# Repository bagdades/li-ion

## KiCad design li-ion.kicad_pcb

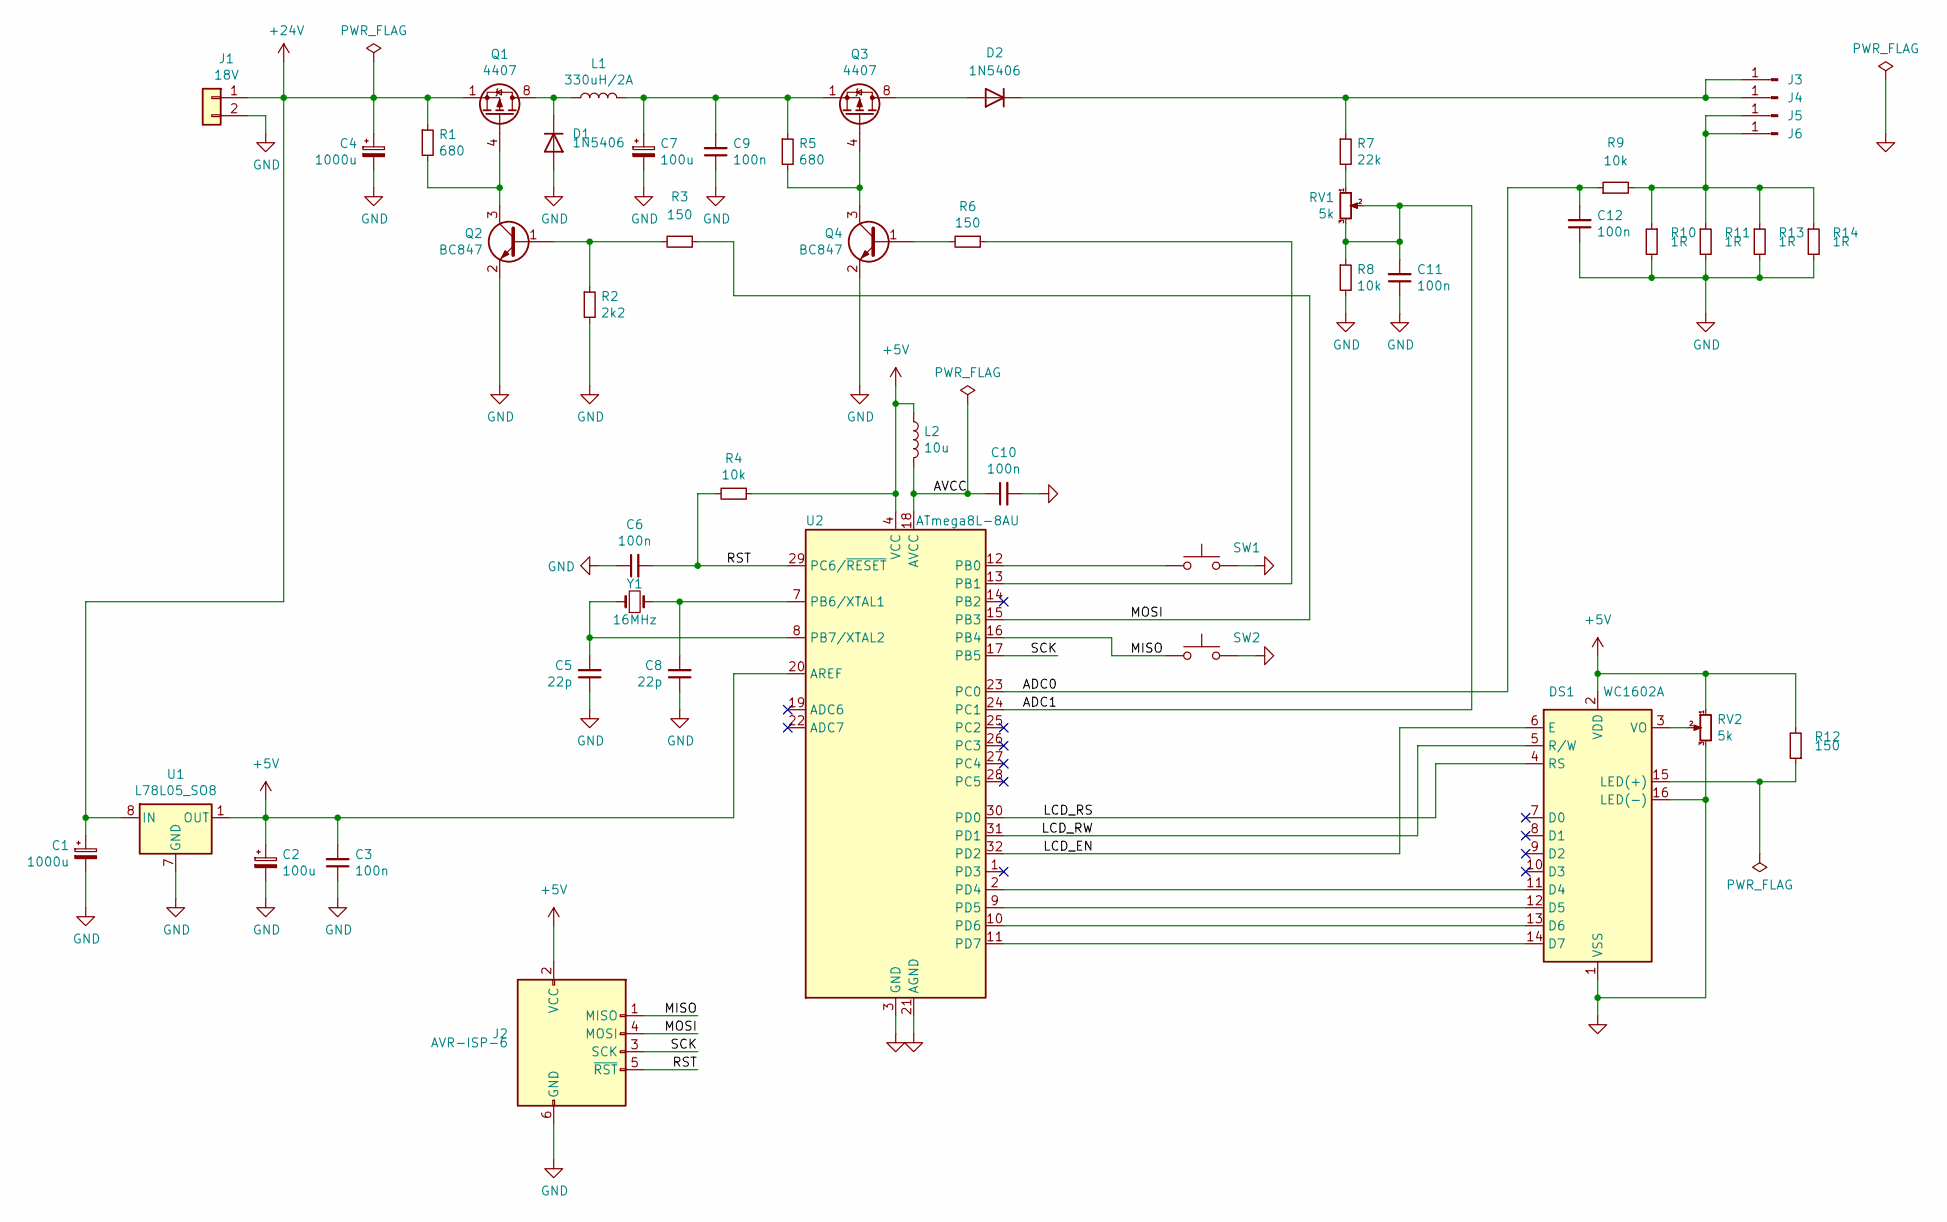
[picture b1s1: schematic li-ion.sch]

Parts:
C1, C4: 1000u; C_Radial_D10.0mm_H16.0mm_P5.00mm
C2: 100u; C_Radial_D8.0mm_H7.0mm_P3.50mm
C3, C6, C9, C10, C11, C12: 100n; C_0805_2012Metric
C5, C8: 22p; C_0603_1608Metric
C7: 100u; C_Radial_D10.0mm_H16.0mm_P5.00mm
D1, D2: 1N5406; D_DO-201AD_P15.24mm_Horizontal
DS1: WC1602A; PinHeader_1x16_P2.54mm_Vertical
J1: 18V; TerminalBlock_Phoenix_MKDS-1,5-2-5.08_1x02_P5.08mm_Horizont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
J2: AVR-ISP-6; PinHeader_2x03_P2.54mm_Vertical
J3, J4, J5, J6: Conn_01x01_Male; PinHeader_1x01_P2.54mm_Vertical
L1: 330uH/2A; L_Radial_D12.0mm_P5.00mm_Fastron_11P
L2: 10u; L_6.3x6.3_H3
Q1, Q3: 4407; SOIC-8_3.9x4.9mm_P1.27mm
Q2, Q4: BC847; SOT-23
R1, R5: 680; R_0805_2012Metric
R2: 2k2; R_0805_2012Metric
R3, R6, R12: 150; R_0805_2012Metric
R4, R8, R9: 10k; R_0805_2012Metric
R7: 22k; R_0805_2012Metric
R10, R11: 1R; R_1206_3216Metric
R13, R14: 1R; R_Axial_DIN0516_L15.5mm_D5.0mm_P20.32mm_Horizontal
RV1, RV2: 5k; Potentiometer_Piher_PT-6-V_Vertical
SW1, SW2: SW_Push; SW_Tactile_SPST_Angled_PTS645Vx58-2LFS
U1: L78L05_SO8; SOIC-8_3.9x4.9mm_P1.27mm
U2: ATmega8L-8AU; TQFP-32_7x7mm_P0.8mm
Y1: 16MHz; Crystal_HC18-U_Vertical

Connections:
+5V: C2.1, C3.2, DS1.2 (VDD), J2.2 (VCC), L2.1, R4.1, R12.2, RV2.1, U1.1 (OUT), U2.4 (VCC), U2.6 (VCC), U2.20 (AREF)
+24V: C1.1, C4.1, J1.1, Q1.1 (S), Q1.2 (S), Q1.3 (S), R1.1, U1.8 (IN)
/ADC0: C12.2, R9.1, U2.23 (PC0)
/ADC1: C11.2, R8.1, RV1.2, RV1.3, U2.24 (PC1)
/AVCC: C10.1, L2.2, U2.18 (AVCC)
/LCD_EN: DS1.6 (E), U2.32 (PD2)
/LCD_RS: DS1.4 (RS), U2.30 (PD0)
/LCD_RW: DS1.5 (R/W), U2.31 (PD1)
/MISO: J2.1 (MISO), SW2.1, U2.16 (PB4)
/MOSI: J2.4 (MOSI), R3.1, U2.15 (PB3)
/RST: C6.2, J2.5 (~RST), R4.2, U2.29 (PC6/~RESET)
/SCK: J2.3 (SCK), U2.17 (PB5)
GND: C1.2, C2.2, C3.1, C4.2, C5.1, C6.1, C7.2, C8.1, C9.1, C10.2, C11.1, C12.1, D1.2 (A), DS1.1 (VSS), DS1.16 (LED(-)), J1.2, J2.6 (GND), Q2.2 (E), Q4.2 (E), R2.2, R8.2, R10.2, R11.2, R13.2, R14.2, RV2.3, SW1.2, SW2.2, U1.2 (GND), U1.3 (GND), U1.6 (GND), U1.7 (GND), U2.3 (GND), U2.5 (GND), U2.21 (AGND)
unnamed: C5.2, U2.8 (PB7/XTAL2), Y1.1
unnamed: C7.1, C9.2, L1.2, Q3.1 (S), Q3.2 (S), Q3.3 (S), R5.1
unnamed: C8.2, U2.7 (PB6/XTAL1), Y1.2
unnamed: D1.1 (K), L1.1, Q1.5 (D), Q1.6 (D), Q1.7 (D), Q1.8 (D)
unnamed: D2.1 (K), J3.1, J4.1, R7.1
unnamed: D2.2 (A), Q3.5 (D), Q3.6 (D), Q3.7 (D), Q3.8 (D)
unnamed: DS1.3 (VO), RV2.2
unnamed: DS1.11 (D4), U2.2 (PD4)
unnamed: DS1.12 (D5), U2.9 (PD5)
unnamed: DS1.13 (D6), U2.10 (PD6)
unnamed: DS1.14 (D7), U2.11 (PD7)
unnamed: DS1.15 (LED(+)), R12.1
unnamed: J5.1, J6.1, R9.2, R10.1, R11.1, R13.1, R14.1
unnamed: Q1.4 (G), Q2.3 (C), R1.2
unnamed: Q2.1 (B), R2.1, R3.2
unnamed: Q3.4 (G), Q4.3 (C), R5.2
unnamed: Q4.1 (B), R6.2
unnamed: R6.1, U2.13 (PB1)
unnamed: R7.2, RV1.1
unnamed: SW1.1, U2.12 (PB0)

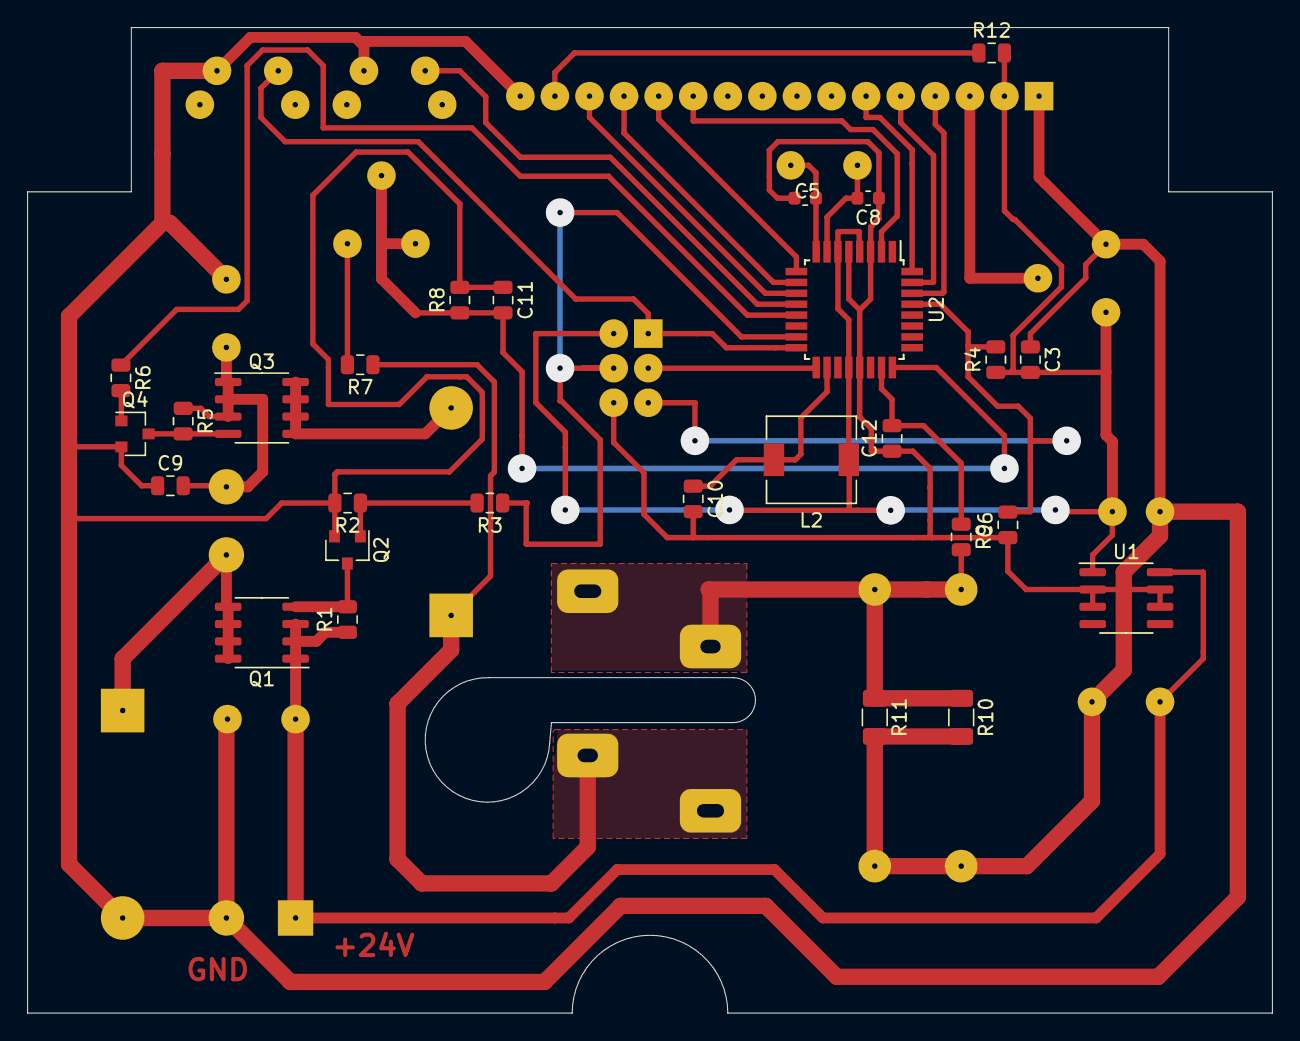
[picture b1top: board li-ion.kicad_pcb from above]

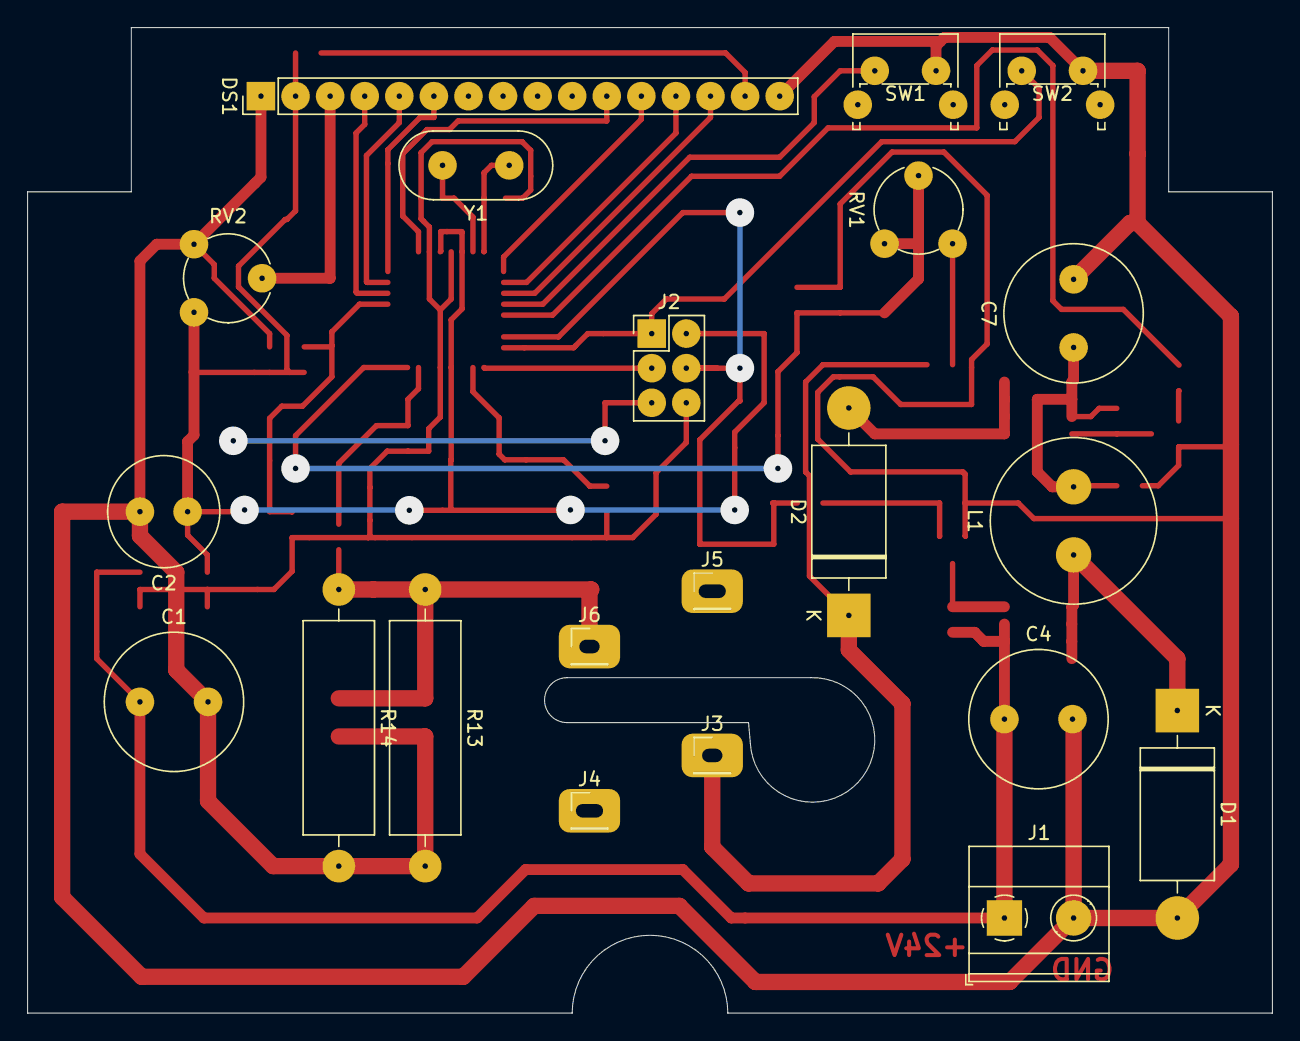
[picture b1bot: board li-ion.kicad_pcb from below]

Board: 2 copper layers, 91.4 x 72.4 mm, 48 parts (21 on the bottom side), 33 nets.

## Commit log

2020-04-16 Final
